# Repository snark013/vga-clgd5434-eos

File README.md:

# Eos VGA Card

[Русская версия](README_RU.md)

Main project repository: [git.snark13.com/snark13/eos](https://git.snark13.com/snark13/eos.git).

GitHub mirror: [github.com/snark013/vga-clgd5434-eos](https://github.com/snark013/vga-clgd5434-eos).

Eos is a VGA graphics card for the 16-bit ISA bus, based on the Cirrus Logic CL-GD5434. The project is designed in KiCad and uses a two-layer PCB.

## Project status

Version 0.7 has been assembled and tested with both 1 MB and 2 MB of video memory.

Release files for version 1.0.2 are available in the repository. This version corrects a device type label in the schematic; the PCB is unchanged. The test results above apply to version 0.7.

## Key features

- VGA compatibility.
- Fast video memory access in MS-DOS.
- Hardware graphics acceleration in Microsoft Windows.
- Integrated video digital-to-analog converter (RAMDAC) with True Color support.
- Two video memory configurations: 1 MB or 2 MB.
- Two-layer PCB for the 16-bit ISA bus.

## Video memory configurations

| Capacity | Chips to populate | Status |
| --- | --- | --- |
| 1 MB | U1, U2 | Tested on the version 0.7 board. |
| 2 MB | U1, U2, U8, U9 | Tested on the version 0.7 board. |

## Project files

- [eos.kicad_pro](eos.kicad_pro) — KiCad project.
- [eos.kicad_sch](eos.kicad_sch) — schematic.
- [eos.kicad_pcb](eos.kicad_pcb) — PCB layout.
- [eos.pretty/](eos.pretty/) — local footprint library.
- [docs/](docs/) — reference documentation.
- [release/](release/) — release files: Gerber files, PDF schematics, and interactive bills of materials.
- [images/0.7/](images/0.7/) — photos of the assembled version 0.7 board.

### Release files

| Version | Gerber files | Schematic | Interactive bill of materials |
| --- | --- | --- | --- |
| 1.0.2 | [ZIP](release/1.0.2/eos-1.0.zip) | [PDF](release/1.0.2/eos.pdf) | [HTML](release/1.0.2/ibom.html) |
| 0.7 | [ZIP](release/0.7/eos.zip) | [PDF](release/0.7/eos.pdf) | [HTML](release/0.7/ibom.html) |

## Configuration and assembly

Check the configuration input settings against the [CL-GD543x/4x Technical Reference Manual](docs/Alpine_VGA_Family_CL-GD543X_4X_Technical_Reference_Manual_4ed_Feb95.pdf).

### Configuration resistors

| Reference | Function |
| --- | --- |
| R39 | DRAM clock selection (50 MHz by default) |
| R40 | Extended RAS timing: 7/6 MCLK |
| R41 | DRAM multi CAS/WE configuration |
| R42 | Sleep control port selection: 3C3h / 4E68h |

Of the resistors listed above, R40 and R42 are fitted by default; R39 and R41 are not fitted.

### Configuration jumpers

| Reference | Function |
| --- | --- |
| JP2 | Zero-wait-state ISA operation |
| JP4 | BIOS ROM section selection |
| JP5 | Enable IRQ2 |
| JP6, JP7 | DDC configuration |

JP2 is fitted by default, and the DDC2B configuration is used.

### DDC support

- DDC2B: fit JP6, JP7, and R27–R30.
- DDC1: fit R26, R28, and R30.

### Clock source

Two options are provided for the 14.318 MHz clock:

- ISA bus BOSC signal: fit R11.
- On-board oscillator: fit Y1.

## BIOS

The assembled board uses a BIOS ROM chip from a PCI graphics card based on the CL-GD5434. This BIOS also works with the ISA board.

Unlike BIOS images for earlier Cirrus Logic graphics chips, the CL-GD543x family BIOS already uses linear (“flat”) addressing. The address conversion described for Helios is not required. Compatibility with other BIOS images must be verified separately.

## Revision history

### 1.0.2

- Corrected the mislabeled U6 device type from 74LS541 to 74LS245.
- The PCB is unchanged.

### 0.7

- Changed all capacitors below 0.1 µF to the 0603 package size.
- Added an alternative 5032 footprint for the 14.318 MHz oscillator.
- Built the first working board version.

### 0.5

- Added support for an on-board 14.318 MHz oscillator in a 7050 package.
- Optimized component placement.
- Renumbered components.

### 0.3

- Initial project version.

## Photos

Assembled version 0.7 board.

## Related projects

- [Pine CL-GD5434](https://github.com/Leshak-pcb/Pine-CL-GD5434) — a graphics card based on the same chip, using a four-layer PCB.

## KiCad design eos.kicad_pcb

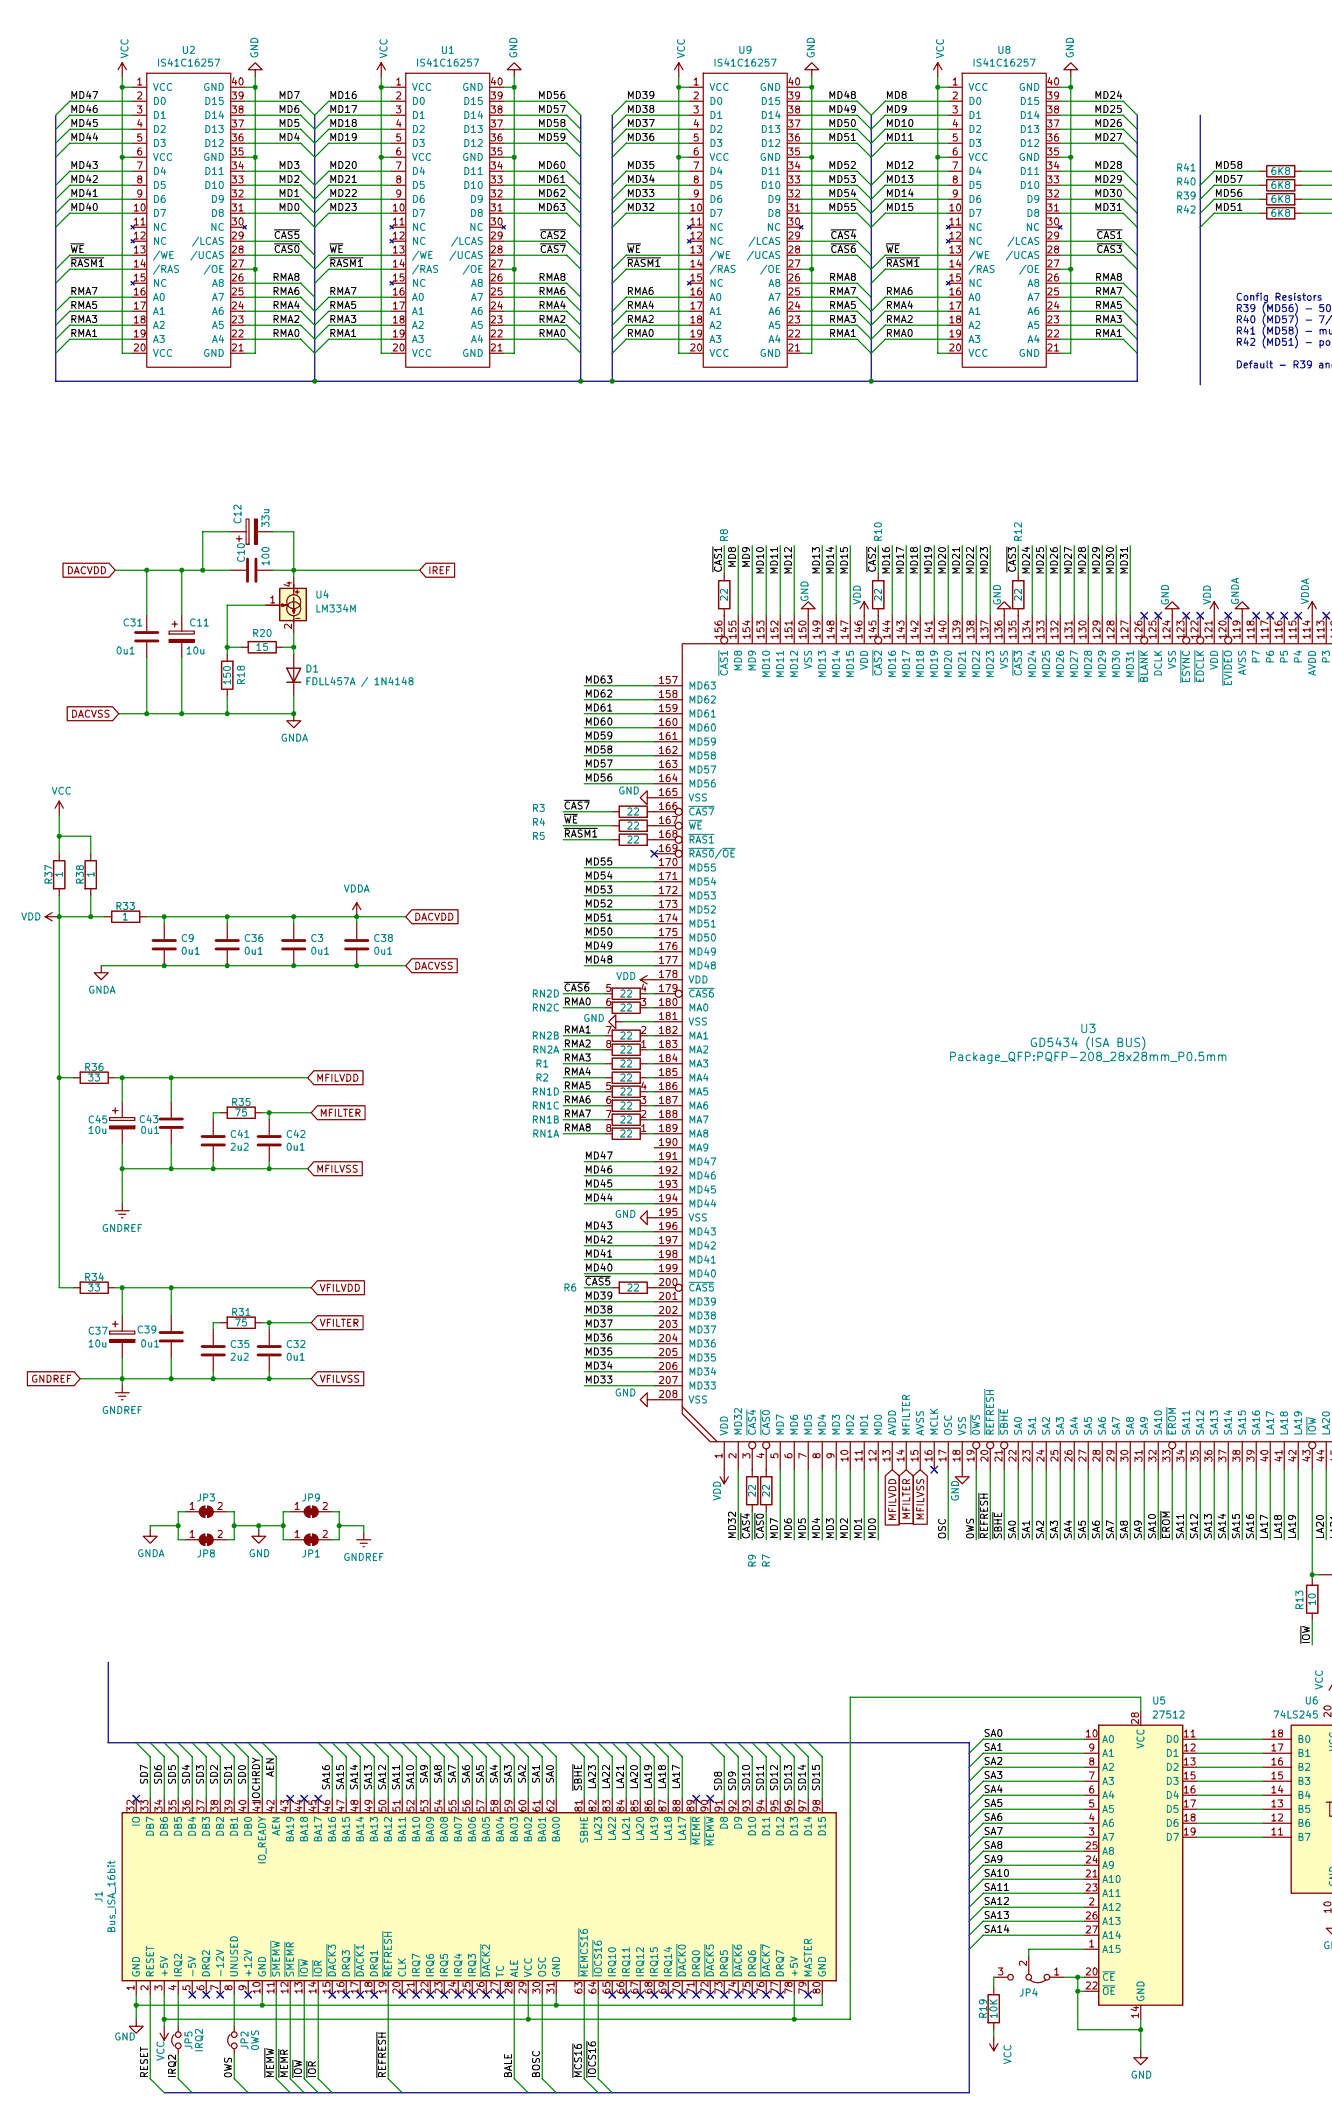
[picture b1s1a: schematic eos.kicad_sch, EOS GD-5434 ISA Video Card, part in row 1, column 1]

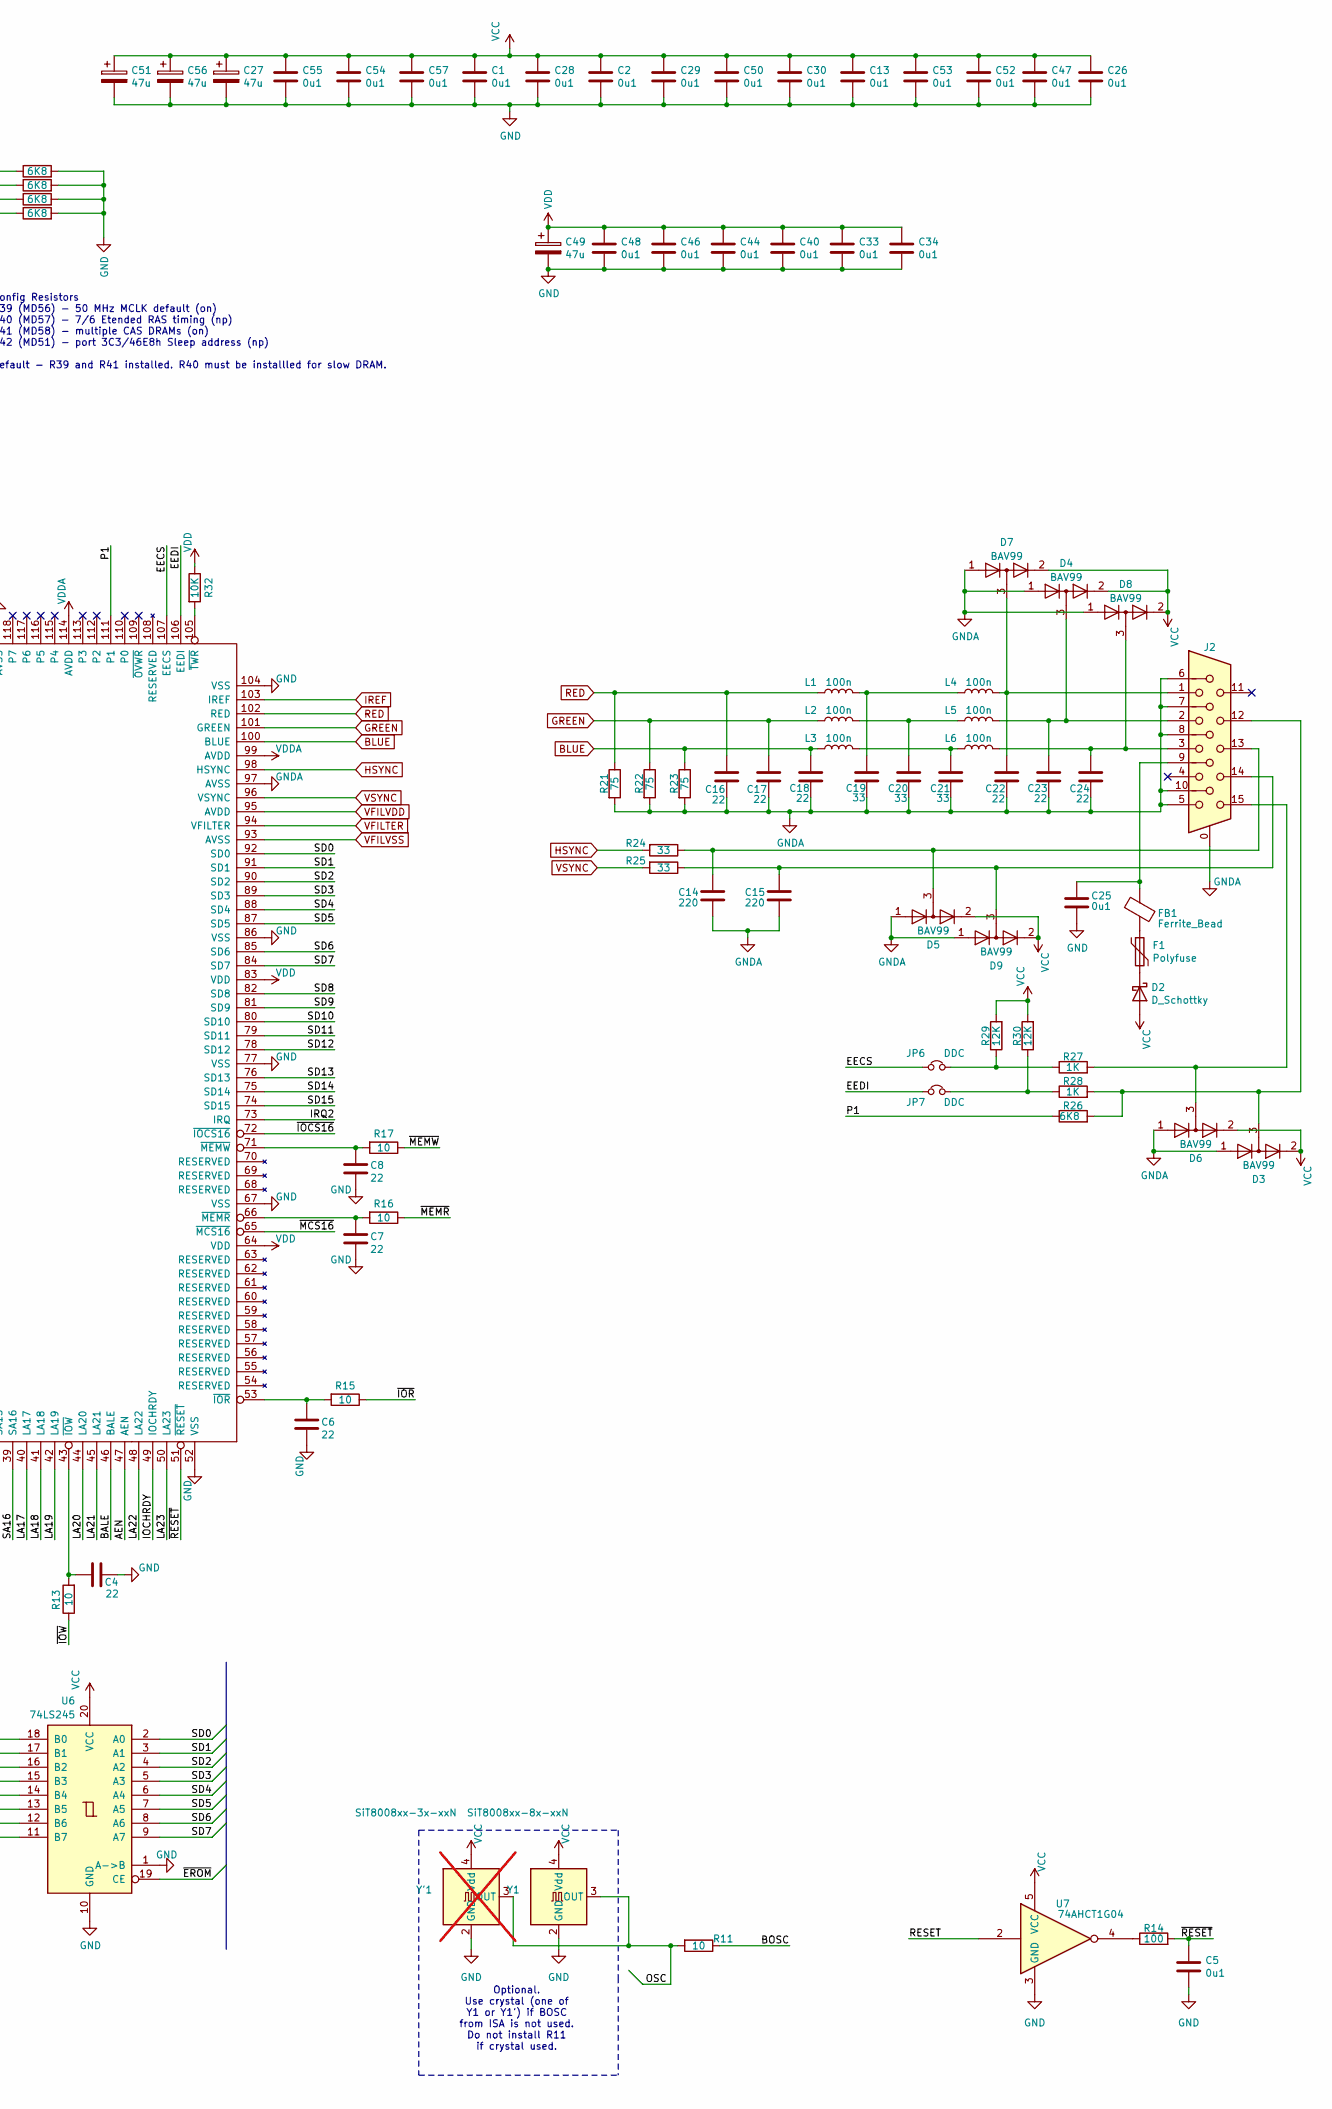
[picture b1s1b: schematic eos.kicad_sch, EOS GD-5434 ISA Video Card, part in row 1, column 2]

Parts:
C1, C2, C3, C5, C9, C13, C25, C26, C28, C29, C30, C31, C32, C33, C34, C36, C38, C39, C40, C42, C43, C44, C46, C47, C48, C50, C52, C53, C54, C55, C57: 0u1; C_0805_2012Metric
C4, C6, C7, C8: 22; C_0402_1005Metric
C10: 100; C_0805_2012Metric
C11, C37, C45: 10u; CP_EIA-3216-18_Kemet-A
C12: 33u; CP_EIA-3216-18_Kemet-A
C14, C15: 220; C_0603_1608Metric
C16, C17, C18, C22, C23, C24: 22; C_0603_1608Metric
C19, C20, C21: 33; C_0603_1608Metric
C27, C49, C51, C56: 47u; CP_EIA-3216-18_Kemet-A
C35, C41: 2u2; C_0805_2012Metric
D1: FDLL457A / 1N4148; D_MiniMELF_Handsoldering
D2: D_Schottky; D_MELF-RM10_Universal_Handsoldering
D3, D4, D5, D6, D7, D8, D9: BAV99; SOT-23
F1: Polyfuse; Fuse_0805_2012Metric_Pad1.15x1.40mm_HandSolder
FB1: Ferrite_Bead; L_0805_2012Metric_Pad1.15x1.40mm_HandSolder
J1: Bus_ISA_16bit; BUS_AT
J2: DB15_Female_HighDensity_MountingHoles; DSUB-15-HD_Female_Horizontal_P2.29x1.98mm_EdgePinOffset3.03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
JP1, JP3, JP8, JP9: SolderJumper_2_Bridged; NonSolderJumper-2_P1.3mm_Bridged2Bar_Pad1.0x1.5mm
JP2: 0WS; PinHeader_1x02_P2.54mm_Vertical
JP4: BIOS Select; PinHeader_1x03_P2.54mm_Vertical
JP5: IRQ2; PinHeader_1x02_P2.54mm_Vertical
JP6, JP7: DDC; SolderJumper-2_P1.3mm_Open_RoundedPad1.0x1.5mm
L1, L2, L3, L4, L5, L6: 100n; L_0805_2012Metric_Pad1.15x1.40mm_HandSolder
R1, R2, R3, R4, R5, R6, R7, R8, R9, R10, R12: 22; R_0402_1005Metric
R11, R13, R15, R16, R17: 10; R_0402_1005Metric
R14: 100; R_0402_1005Metric
R18: 150; R_0603_1608Metric
R19: 10K; R_0603_1608Metric
R20: 15; R_0603_1608Metric
R21, R22, R23: 75; R_0603_1608Metric
R24, R25: 33; R_0603_1608Metric
R26: 6K8; R_0603_1608Metric
R27, R28: 1K; R_0603_1608Metric
R29, R30: 12K; R_0603_1608Metric
R31, R35: 75; R_0805_2012Metric
R32: 10K; R_0805_2012Metric
R33, R37, R38: 1; R_0805_2012Metric
R34, R36: 33; R_0805_2012Metric
R39, R40, R41, R42: 6K8; R_0402_1005Metric
RN1, RN2: 22; R_Array_Convex_4x0603
U1, U2, U8, U9: IS41C16257; SOJ-40-Socket-LongPads
U3: GD5434 (ISA BUS); PQFP-208_28x28mm_P0.5mm
U4: LM334M; SOIC-8_3.9x4.9mm_P1.27mm
U5: 27512; DIP-28_W15.24mm
U6: 74LS245; DIP-20_W7.62mm
U7: 74AHCT1G04; TSOT-23-5_HandSoldering
Y1: SiT8008xx-8x-xxN; Oscillator_SMD_SeikoEpson_SG8002CA-4Pin_7.0x5.0mm
Y'1: SiT8008xx-3x-xxN; Oscillator_SMD_TXC_7C-4Pin_5.0x3.2mm_HandSoldering; not fitted

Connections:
/0WS: JP2.1, U3.19 (~0WS)
/AEN: J1.42 (AEN), U3.47 (AEN)
/BALE: J1.28 (ALE), U3.46 (BALE)
/BOSC: J1.30 (OSC), R11.1
/EECS: JP6.1, U3.107 (EECS)
/EEDI: JP7.1, U3.106 (EEDI)
/IOCHRDY: J1.41 (IO_READY), U3.49 (IOCHRDY)
/IRQ2: JP5.1, U3.73 (IRQ)
/LA17: J1.88 (LA17), U3.40 (LA17)
/LA18: J1.87 (LA18), U3.41 (LA18)
/LA19: J1.86 (LA19), U3.42 (LA19)
/LA20: J1.85 (LA20), U3.44 (LA20)
/LA21: J1.84 (LA21), U3.45 (LA21)
/LA22: J1.83 (LA22), U3.48 (LA22)
/LA23: J1.82 (LA23), U3.50 (LA23)
/MD0: U2.31 (D8), U3.12 (MD0)
/MD1: U2.32 (D9), U3.11 (MD1)
/MD2: U2.33 (D10), U3.10 (MD2)
/MD3: U2.34 (D11), U3.9 (MD3)
/MD4: U2.36 (D12), U3.8 (MD4)
/MD5: U2.37 (D13), U3.7 (MD5)
/MD6: U2.38 (D14), U3.6 (MD6)
/MD7: U2.39 (D15), U3.5 (MD7)
/MD8: U3.155 (MD8), U8.2 (D0)
/MD9: U3.154 (MD9), U8.3 (D1)
/MD10: U3.153 (MD10), U8.4 (D2)
/MD11: U3.152 (MD11), U8.5 (D3)
/MD12: U3.151 (MD12), U8.7 (D4)
/MD13: U3.149 (MD13), U8.8 (D5)
/MD14: U3.148 (MD14), U8.9 (D6)
/MD15: U3.147 (MD15), U8.10 (D7)
/MD16: U1.2 (D0), U3.144 (MD16)
/MD17: U1.3 (D1), U3.143 (MD17)
/MD18: U1.4 (D2), U3.142 (MD18)
/MD19: U1.5 (D3), U3.141 (MD19)
/MD20: U1.7 (D4), U3.140 (MD20)
/MD21: U1.8 (D5), U3.139 (MD21)
/MD22: U1.9 (D6), U3.138 (MD22)
/MD23: U1.10 (D7), U3.137 (MD23)
/MD24: U3.134 (MD24), U8.39 (D15)
/MD25: U3.133 (MD25), U8.38 (D14)
/MD26: U3.132 (MD26), U8.37 (D13)
/MD27: U3.131 (MD27), U8.36 (D12)
/MD28: U3.130 (MD28), U8.34 (D11)
/MD29: U3.129 (MD29), U8.33 (D10)
/MD30: U3.128 (MD30), U8.32 (D9)
/MD31: U3.127 (MD31), U8.31 (D8)
/MD32: U3.2 (MD32), U9.10 (D7)
/MD33: U3.207 (MD33), U9.9 (D6)
/MD34: U3.206 (MD34), U9.8 (D5)
/MD35: U3.205 (MD35), U9.7 (D4)
/MD36: U3.204 (MD36), U9.5 (D3)
/MD37: U3.203 (MD37), U9.4 (D2)
/MD38: U3.202 (MD38), U9.3 (D1)
/MD39: U3.201 (MD39), U9.2 (D0)
/MD40: U2.10 (D7), U3.199 (MD40)
/MD41: U2.9 (D6), U3.198 (MD41)
/MD42: U2.8 (D5), U3.197 (MD42)
/MD43: U2.7 (D4), U3.196 (MD43)
/MD44: U2.5 (D3), U3.194 (MD44)
/MD45: U2.4 (D2), U3.193 (MD45)
/MD46: U2.3 (D1), U3.192 (MD46)
/MD47: U2.2 (D0), U3.191 (MD47)
/MD48: U3.177 (MD48), U9.39 (D15)
/MD49: U3.176 (MD49), U9.38 (D14)
/MD50: U3.175 (MD50), U9.37 (D13)
/MD51: R42.1, U3.174 (MD51), U9.36 (D12)
/MD52: U3.173 (MD52), U9.34 (D11)
/MD53: U3.172 (MD53), U9.33 (D10)
/MD54: U3.171 (MD54), U9.32 (D9)
/MD55: U3.170 (MD55), U9.31 (D8)
/MD56: R39.1, U1.39 (D15), U3.164 (MD56)
/MD57: R40.1, U1.38 (D14), U3.163 (MD57)
/MD58: R41.1, U1.37 (D13), U3.162 (MD58)
/MD59: U1.36 (D12), U3.161 (MD59)
/MD60: U1.34 (D11), U3.160 (MD60)
/MD61: U1.33 (D10), U3.159 (MD61)
/MD62: U1.32 (D9), U3.158 (MD62)
/MD63: U1.31 (D8), U3.157 (MD63)
/OSC: R11.2, U3.17 (OSC), Y1.3 (OUT), Y'1.3 (OUT)
/P1: R26.1, U3.111 (P1)
/RESET: J1.2 (RESET), U7.2
/RMA0: RN2.6 (R3.2), U1.22 (A4), U2.22 (A4), U8.19 (A3), U9.19 (A3)
/RMA1: RN2.7 (R2.2), U1.19 (A3), U2.19 (A3), U8.22 (A4), U9.22 (A4)
/RMA2: RN2.8 (R1.2), U1.23 (A5), U2.23 (A5), U8.18 (A2), U9.18 (A2)
/RMA3: R1.1, U1.18 (A2), U2.18 (A2), U8.23 (A5), U9.23 (A5)
/RMA4: R2.1, U1.24 (A6), U2.24 (A6), U8.17 (A1), U9.17 (A1)
/RMA5: RN1.5 (R4.2), U1.17 (A1), U2.17 (A1), U8.24 (A6), U9.24 (A6)
/RMA6: RN1.6 (R3.2), U1.25 (A7), U2.25 (A7), U8.16 (A0), U9.16 (A0)
/RMA7: RN1.7 (R2.2), U1.16 (A0), U2.16 (A0), U8.25 (A7), U9.25 (A7)
/RMA8: RN1.8 (R1.2), U1.26 (A8), U2.26 (A8), U8.26 (A8), U9.26 (A8)
/SA0: J1.62 (BA00), U3.22 (SA0), U5.10 (A0)
/SA1: J1.61 (BA01), U3.23 (SA1), U5.9 (A1)
/SA2: J1.60 (BA02), U3.24 (SA2), U5.8 (A2)
/SA3: J1.59 (BA03), U3.25 (SA3), U5.7 (A3)
/SA4: J1.58 (BA04), U3.26 (SA4), U5.6 (A4)
/SA5: J1.57 (BA05), U3.27 (SA5), U5.5 (A5)
/SA6: J1.56 (BA06), U3.28 (SA6), U5.4 (A6)
/SA7: J1.55 (BA07), U3.29 (SA7), U5.3 (A7)
/SA8: J1.54 (BA08), U3.30 (SA8), U5.25 (A8)
/SA9: J1.53 (BA09), U3.31 (SA9), U5.24 (A9)
/SA10: J1.52 (BA10), U3.32 (SA10), U5.21 (A10)
/SA11: J1.51 (BA11), U3.34 (SA11), U5.23 (A11)
/SA12: J1.50 (BA12), U3.35 (SA12), U5.2 (A12)
/SA13: J1.49 (BA13), U3.36 (SA13), U5.26 (A13)
/SA14: J1.48 (BA14), U3.37 (SA14), U5.27 (A14)
/SA15: J1.47 (BA15), U3.38 (SA15)
/SA16: J1.46 (BA16), U3.39 (SA16)
/SD0: J1.40 (DB0), U3.92 (SD0), U6.2 (A0)
/SD1: J1.39 (DB1), U3.91 (SD1), U6.3 (A1)
/SD2: J1.38 (DB2), U3.90 (SD2), U6.4 (A2)
/SD3: J1.37 (DB3), U3.89 (SD3), U6.5 (A3)
/SD4: J1.36 (DB4), U3.88 (SD4), U6.6 (A4)
/SD5: J1.35 (DB5), U3.87 (SD5), U6.7 (A5)
/SD6: J1.34 (DB6), U3.85 (SD6), U6.8 (A6)
/SD7: J1.33 (DB7), U3.84 (SD7), U6.9 (A7)
/SD8: J1.91 (D8), U3.82 (SD8)
/SD9: J1.92 (D9), U3.81 (SD9)
/SD10: J1.93 (D10), U3.80 (SD10)
/SD11: J1.94 (D11), U3.79 (SD11)
/SD12: J1.95 (D12), U3.78 (SD12)
/SD13: J1.96 (D13), U3.76 (SD13)
/SD14: J1.97 (D14), U3.75 (SD14)
/SD15: J1.98 (D15), U3.74 (SD15)
/~CAS0: R7.1, U2.28 (/UCAS)
/~CAS1: R8.2, U8.29 (/LCAS)
/~CAS2: R10.2, U1.29 (/LCAS)
/~CAS3: R12.2, U8.28 (/UCAS)
/~CAS4: R9.1, U9.29 (/LCAS)
/~CAS5: R6.2, U2.29 (/LCAS)
/~CAS6: RN2.5 (R4.2), U9.28 (/UCAS)
/~CAS7: R3.1, U1.28 (/UCAS)
/~EROM: U3.33 (~EROM), U6.19 (CE)
/~IOCS16: J1.64 (~IOCS16), U3.72 (~IOCS16)
/~IOR: J1.14 (~IOR), R15.1
/~IOW: J1.13 (~IOW), R13.1
/~MCS16: J1.63 (~MEMCS16), U3.65 (~MCS16)
/~MEMR: J1.12 (~SMEMR), R16.1
/~MEMW: J1.11 (~SMEMW), R17.1
/~RASM1: R5.1, U1.14 (/RAS), U2.14 (/RAS), U8.14 (/RAS), U9.14 (/RAS)
/~REFRESH: J1.19 (~REFRESH), U3.20 (~REFRESH)
/~RESET: C5.1, R14.2, U3.51 (~RESET)
/~SBHE: J1.81 (SBHE), U3.21 (~SBHE)
/~WE: R4.1, U1.13 (/WE), U2.13 (/WE), U8.13 (/WE), U9.13 (/WE)
BLUE: C18.1, L3.1, R23.1, U3.100 (BLUE)
DACVDD: C3.1, C9.1, C10.1, C11.1, C12.1, C31.1, C36.1, C38.1, R33.2, U3.99 (AVDD), U3.114 (AVDD)
DACVSS: C3.2, C9.2, C11.2, C14.2, C15.2, C16.2, C17.2, C18.2, C19.2, C20.2, C21.2, C22.2, C23.2, C24.2, C31.2, C36.2, C38.2, D1.1 (K), D3.1 (K), D4.1 (K), D5.1 (K), D6.1 (K), D7.1 (K), D8.1 (K), D9.1 (K), J2.0, J2.5, J2.6, J2.7, J2.8, J2.10, JP3.1 (A), JP8.1 (A), R18.1, R21.2, R22.2, R23.2, U3.97 (AVSS), U3.119 (AVSS)
GND: C1.2, C2.2, C4.1, C5.2, C6.2, C7.2, C8.2, C13.2, C25.2, C26.2, C27.2, C28.2, C29.2, C30.2, C33.2, C34.2, C40.2, C44.2, C46.2, C47.2, C48.2, C49.2, C50.2, C51.2, C52.2, C53.2, C54.2, C55.2, C56.2, C57.2, J1.1 (GND), J1.10 (GND), J1.31 (GND), J1.80 (GND), JP1.1 (A), JP3.2 (B), JP4.1 (A), JP8.2 (B), JP9.1 (A), R39.2, R40.2, R41.2, R42.2, U1.21 (GND), U1.27 (/OE), U1.35 (GND), U1.40 (GND), U2.21 (GND), U2.27 (/OE), U2.35 (GND), U2.40 (GND), U3.18 (VSS), U3.52 (VSS), U3.67 (VSS), U3.77 (VSS), U3.86 (VSS), U3.104 (VSS), U3.124 (VSS), U3.136 (VSS), U3.150 (VSS), U3.165 (VSS), U3.181 (VSS), U3.195 (VSS), U3.208 (VSS), U5.14 (GND), U5.20 (~CE), U5.22 (~OE), U6.1 (A->B), U6.10 (GND), U7.3 (GND), U8.21 (GND), U8.27 (/OE), U8.35 (GND), U8.40 (GND), U9.21 (GND), U9.27 (/OE), U9.35 (GND), U9.40 (GND), Y1.2 (GND), Y'1.2 (GND)
GNDREF: C32.2, C35.2, C37.2, C39.2, C41.2, C42.2, C43.2, C45.2, JP1.2 (B), JP9.2 (B), U3.15 (AVSS), U3.93 (AVSS)
GREEN: C17.1, L2.1, R22.1, U3.101 (GREEN)
HSYNC: R24.2, U3.98 (HSYNC)
IREF: C10.2, C12.2, U3.103 (IREF), U4.4
MFILTER: C42.1, R35.1, U3.14 (MFILTER)
MFILVDD: C43.1, C45.1, R36.1, U3.13 (AVDD)
unnamed: C14.1, D5.3 (K), J2.13, R24.1
unnamed: C15.1, D9.3 (K), J2.14, R25.1
unnamed: C19.1, L1.2, L4.1
unnamed: C20.1, L2.2, L5.1
unnamed: C21.1, L3.2, L6.1
unnamed: C22.1, D7.3 (K), J2.1, L4.2
unnamed: C23.1, D4.3 (K), J2.2, L5.2
unnamed: C24.1, D8.3 (K), J2.3, L6.2
unnamed: C25.1, FB1.1, J2.9
unnamed: C35.1, R31.2
unnamed: C41.1, R35.2
unnamed: D1.2 (A), R20.1, U4.2, U4.3, U4.6, U4.7
unnamed: D2.1 (K), F1.2
unnamed: D3.3 (K), J2.12, R26.2, R28.2
unnamed: D6.3 (K), J2.15, R27.2
unnamed: F1.1, FB1.2
unnamed: J1.4 (IRQ2), JP5.2
unnamed: J1.8 (UNUSED), JP2.2
unnamed: JP4.3 (B), R19.1
unnamed: JP4.2 (C), U5.1 (A15)
unnamed: JP6.2, R27.1, R29.1
unnamed: JP7.2, R28.1, R30.1
unnamed: R14.1, U7.4
unnamed: R18.2, R20.2, U4.1
unnamed: RN1.1 (R1.1), U3.189 (MA8)
unnamed: RN1.2 (R2.1), U3.188 (MA7)
unnamed: RN1.3 (R3.1), U3.187 (MA6)
unnamed: RN1.4 (R4.1), U3.186 (MA5)
unnamed: RN2.1 (R1.1), U3.183 (MA2)
unnamed: RN2.2 (R2.1), U3.182 (MA1)
unnamed: RN2.3 (R3.1), U3.180 (MA0)
unnamed: RN2.4 (R4.1), U3.179 (~CAS6)
unnamed: R1.2, U3.184 (MA3)
unnamed: R2.2, U3.185 (MA4)
unnamed: R7.2, U3.4 (~CAS0)
unnamed: R8.1, U3.156 (~CAS1)
unnamed: R10.1, U3.145 (~CAS2)
unnamed: R12.1, U3.135 (~CAS3)
unnamed: R9.2, U3.3 (~CAS4)
unnamed: R6.1, U3.200 (~CAS5)
unnamed: R3.2, U3.166 (~CAS7)
unnamed: C6.1, R15.2, U3.53 (~IOR)
unnamed: C4.2, R13.2, U3.43 (~IOW)
unnamed: C7.1, R16.2, U3.66 (~MEMR)
unnamed: C8.1, R17.2, U3.71 (~MEMW)
unnamed: R5.2, U3.168 (~RAS1)
unnamed: R32.2, U3.105 (~TWR)
unnamed: R4.2, U3.167 (~WE)
unnamed: U5.11 (D0), U6.18 (B0)
unnamed: U5.12 (D1), U6.17 (B1)
unnamed: U5.13 (D2), U6.16 (B2)
unnamed: U5.15 (D3), U6.15 (B3)
unnamed: U5.16 (D4), U6.14 (B4)
unnamed: U5.17 (D5), U6.13 (B5)
unnamed: U5.18 (D6), U6.12 (B6)
unnamed: U5.19 (D7), U6.11 (B7)
RED: C16.1, L1.1, R21.1, U3.102 (RED)
VCC: C1.1, C2.1, C13.1, C26.1, C27.1, C28.1, C29.1, C30.1, C47.1, C50.1, C51.1, C52.1, C53.1, C54.1, C55.1, C56.1, C57.1, D2.2 (A), D3.2 (A), D4.2 (A), D5.2 (A), D6.2 (A), D7.2 (A), D8.2 (A), D9.2 (A), J1.3 (+5V), J1.29 (VCC), J1.78 (+5V), R19.2, R29.2, R30.2, R37.1, R38.1, U1.1 (VCC), U1.6 (VCC), U1.20 (VCC), U2.1 (VCC), U2.6 (VCC), U2.20 (VCC), U5.28 (VCC), U6.20 (VCC), U7.5 (VCC), U8.1 (VCC), U8.6 (VCC), U8.20 (VCC), U9.1 (VCC), U9.6 (VCC), U9.20 (VCC), Y1.4 (Vdd), Y'1.4 (Vdd)
VDD: C33.1, C34.1, C40.1, C44.1, C46.1, C48.1, C49.1, R32.1, R33.1, R34.2, R36.2, R37.2, R38.2, U3.1 (VDD), U3.64 (VDD), U3.83 (VDD), U3.121 (VDD), U3.146 (VDD), U3.178 (VDD)
VFILTER: C32.1, R31.1, U3.94 (VFILTER)
VFILVDD: C37.1, C39.1, R34.1, U3.95 (AVDD)
VSYNC: R25.2, U3.96 (VSYNC)

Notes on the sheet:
Config Resistors R39 (MD56) - 50 MHz MCLK default (on) R40 (MD57) - 7/6 Etended RAS timing (np) R41 (MD58) - multiple CAS DRAMs (on) R42 (MD51) - port 3C3/46E8h Sleep address (np) Default - R39 and R41 installed. R40 must be installled for slow DRAM.
Optional. Use crystal (one of Y1 or Y1') if BOSC from ISA is not used. Do not install R11 if crystal used.

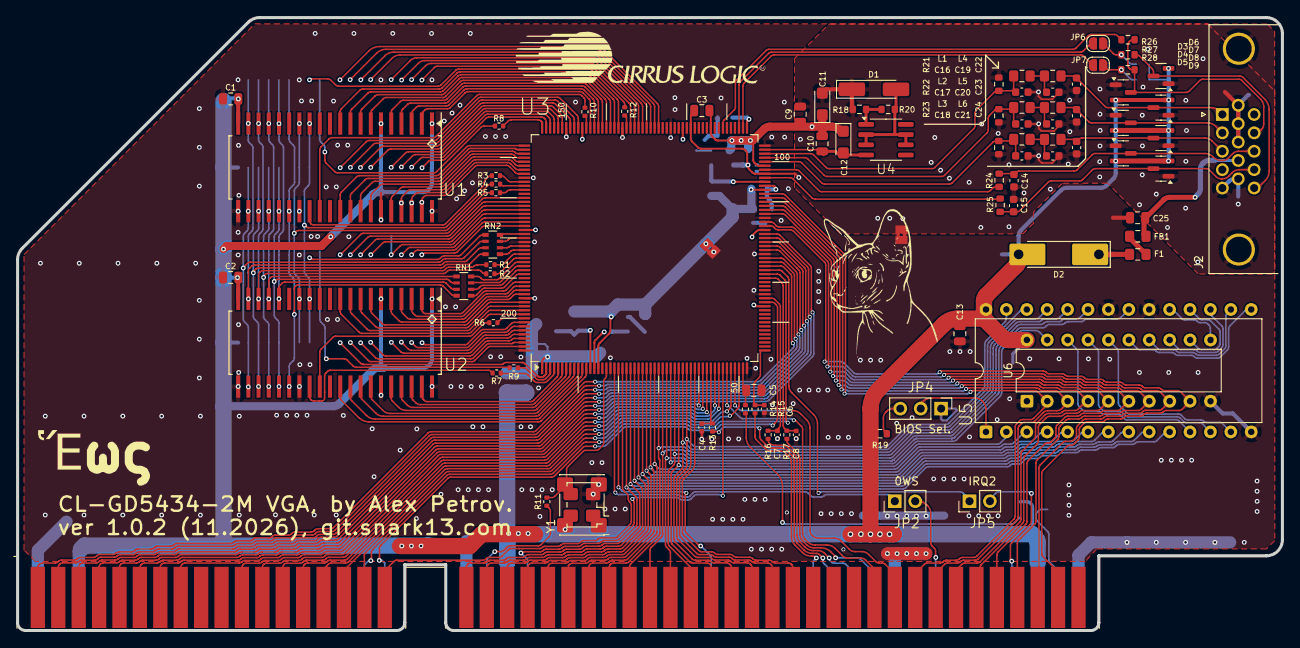
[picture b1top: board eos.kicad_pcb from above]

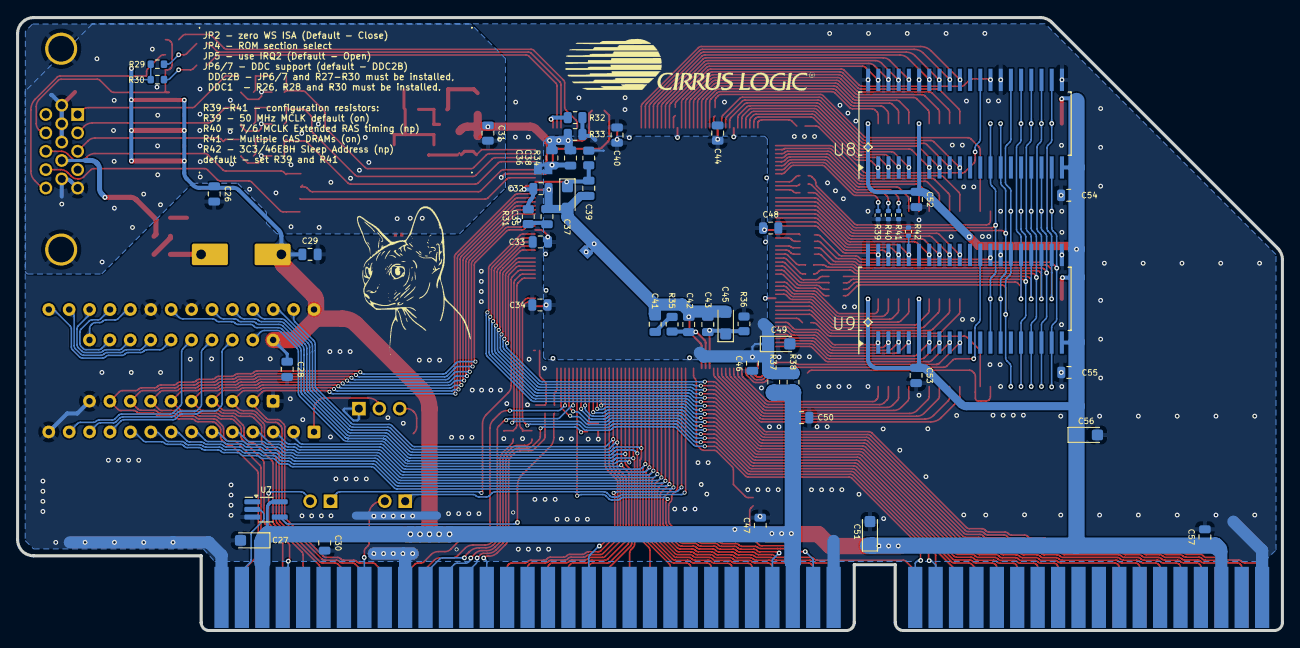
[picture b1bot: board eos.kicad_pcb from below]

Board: 2 copper layers, 157.4 x 76.3 mm, 140 parts (51 on the bottom side), 216 nets.

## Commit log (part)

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2025-09-13 Initial build.
2025-09-13 ChangeLog: - 0.7 release
2025-09-13 release files update.
2025-09-13 Release 0.7
